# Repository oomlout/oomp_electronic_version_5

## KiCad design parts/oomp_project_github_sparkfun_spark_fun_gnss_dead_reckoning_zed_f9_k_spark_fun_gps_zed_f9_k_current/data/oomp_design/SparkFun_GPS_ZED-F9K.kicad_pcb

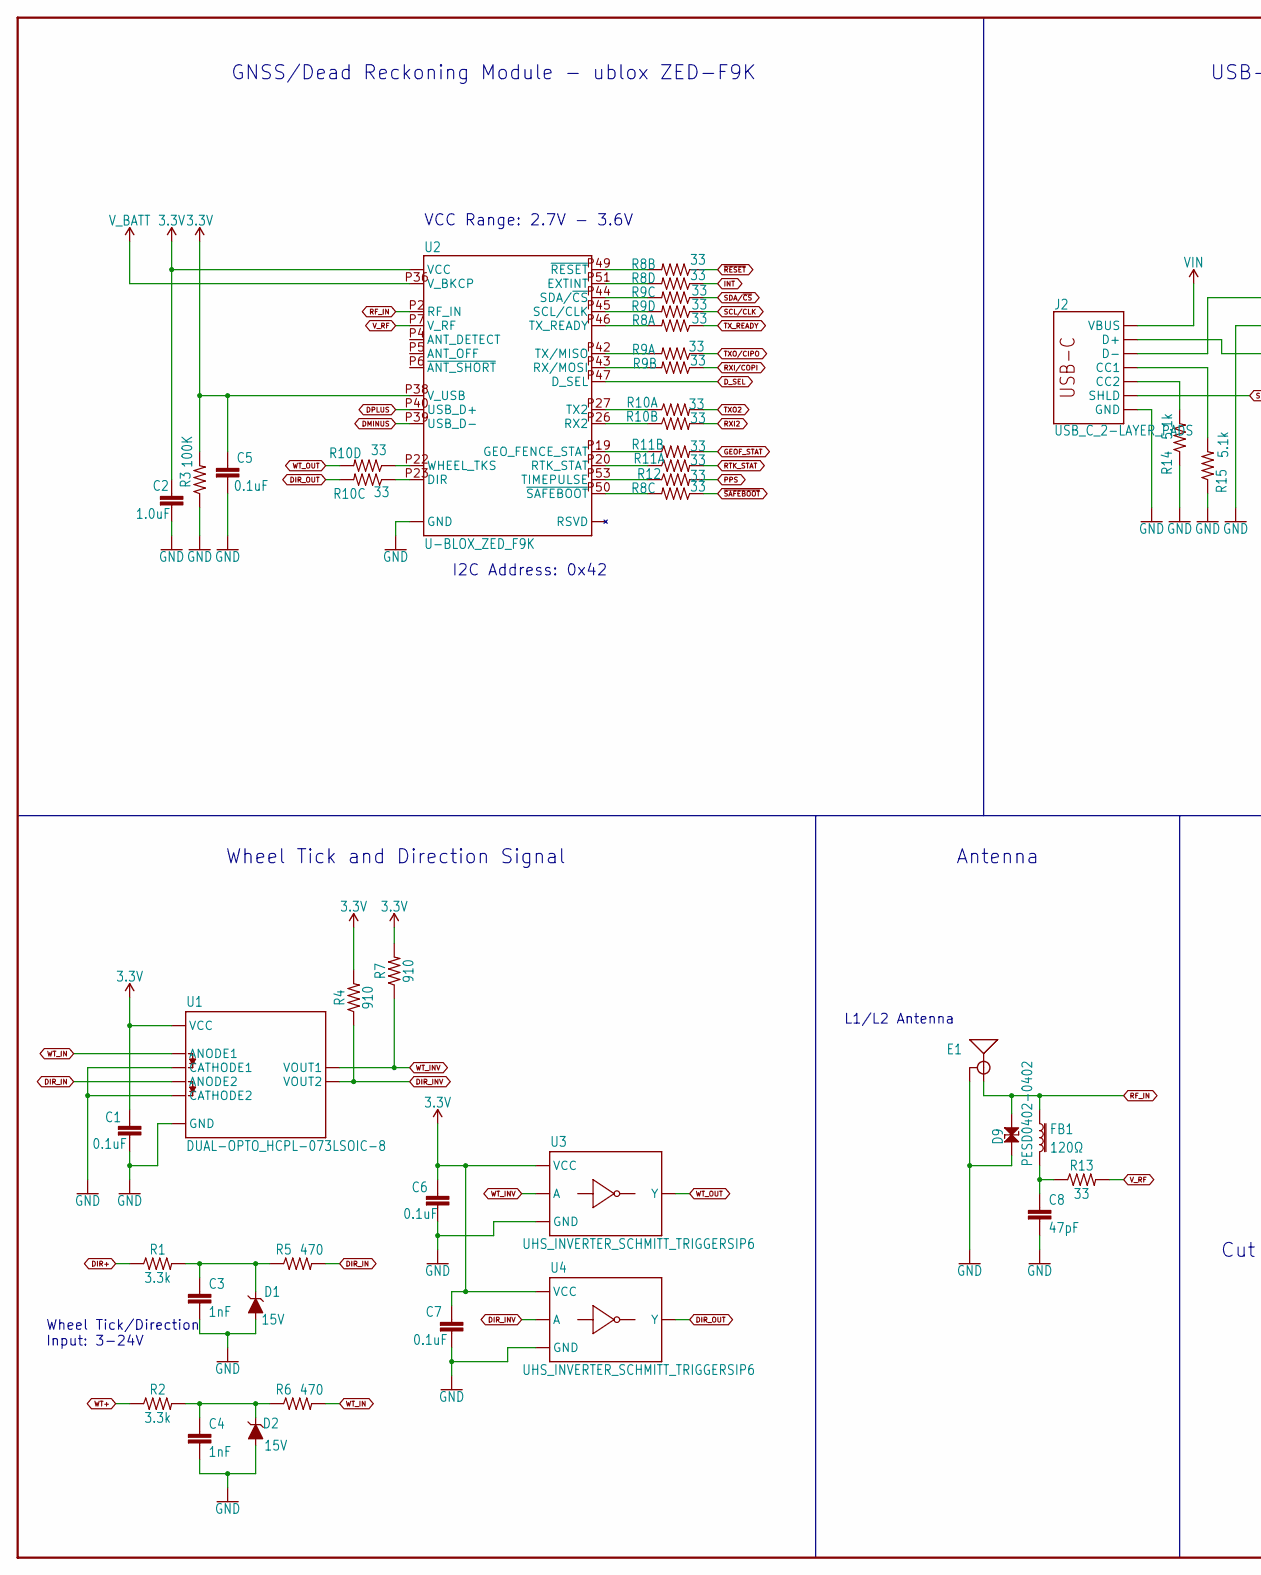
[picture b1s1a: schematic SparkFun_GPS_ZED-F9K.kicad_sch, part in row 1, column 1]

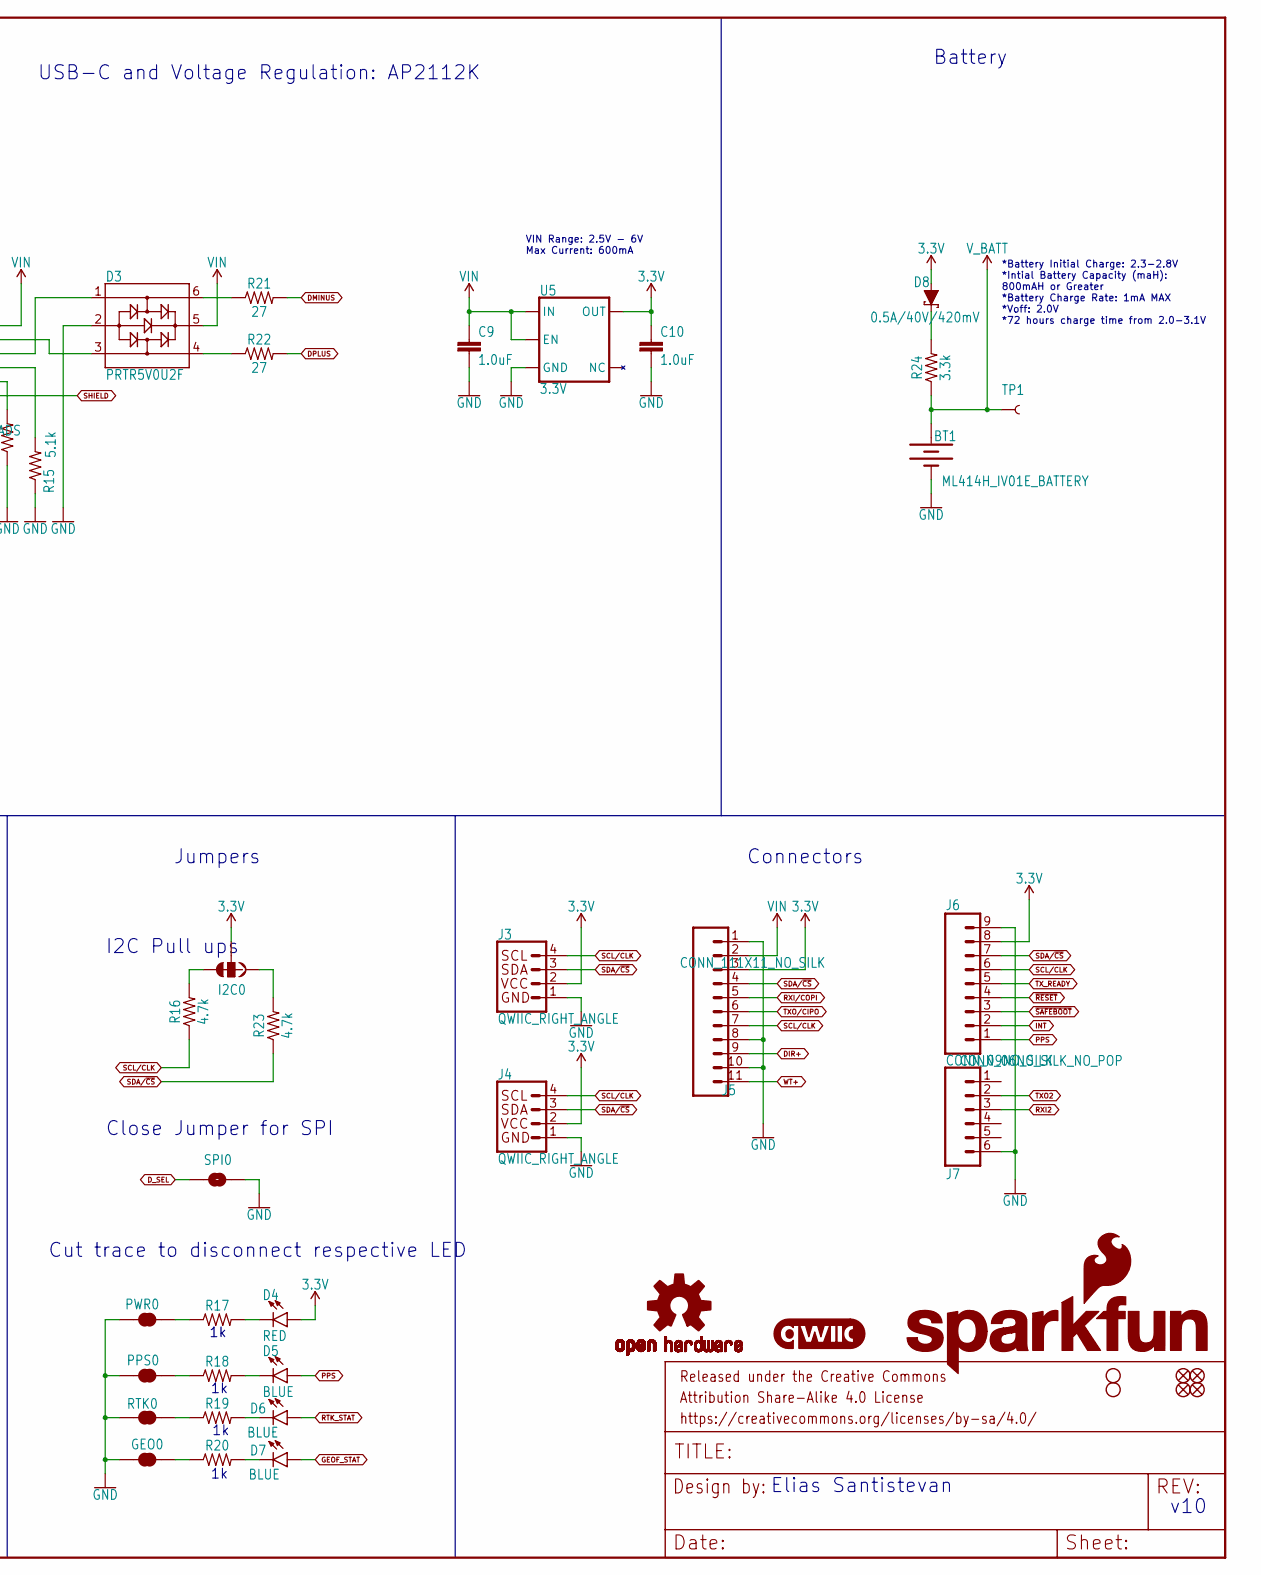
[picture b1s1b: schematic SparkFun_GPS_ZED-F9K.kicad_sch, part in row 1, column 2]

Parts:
$1_25_$_2020-03-30_22-52-05: STAND-OFFTIGHT; STAND-OFF-TIGHT
BT1: ML414H_IV01E_BATTERY; ML414H_IV01E
C1, C5, C6, C7: 0.1uF; 0402-TIGHT
C2, C9, C10: 1.0uF; 0402-TIGHT
C3, C4: 1nF; 0402
C8: 47pF; 0402
D1, D2: 15V; SOT23-3
D3: PRTR5V0U2F; SOT886
D4: RED; LED-0603
D5, D6, D7: BLUE; LED-0603
D8: 0.5A/40V/420mV; SOD-323
D9: PESD0402-0402; 0402; MOUSE_PART 650-PESD0402-140; DIGIKEY_PART PESD0402-140CT-ND
E1: ANTENNA-SMA-GROUNDEDEDGE_SMA; SMA-EDGE
FB1: 120Ω; 0402; MFG_PART BLM15HB121SN1D
FD1, FD2, FD3, FD4: FIDUCIALUFIDUCIAL; FIDUCIAL-MICRO
FRAME1: FRAME-LEDGER; CREATIVE_COMMONS
GEO0: JUMPER-SMT_2_NC_TRACE_SILK; SMT-JUMPER_2_NC_TRACE_SILK
H2: STAND-OFFTIGHT; STAND-OFF-TIGHT
I2C0: JUMPER-SMT_3_2-NC_TRACE_SILK; SMT-JUMPER_3_2-NC_TRACE_SILK
J2: USB_C_2-LAYER_PADS; USB-C-16P-2LAYER-PADS
J3, J4: QWIIC_RIGHT_ANGLE; JST04_1MM_RA
J5: CONN_111X11_NO_SILK; 1X11_NO_SILK
J6: CONN_09NO_SILK; 1X09_NO_SILK
J7: CONN_06NO_SILK_NO_POP; 1X06_NO_SILK
LOGO1: OSHW-LOGOS; OSHW-LOGO-S
LOGO2: QWIIC_LOGO_4MM; QWIIC_4MM
LOGO3: SFE_LOGO_NAME_FLAME.2_INCH; SFE_LOGO_NAME_FLAME_.2
PPS0: JUMPER-SMT_2_NC_TRACE_SILK; SMT-JUMPER_2_NC_TRACE_SILK
PWR0: JUMPER-SMT_2_NC_TRACE_SILK; SMT-JUMPER_2_NC_TRACE_SILK
R1, R2, R24: 3.3k; 0603
R3: 100K; 0402
R4, R7: 910; 0603
R5, R6: 470; 0603
R8, R9, R10, R11: 33; 1206_RA
R12, R13: 33; 0603
R14, R15: 5.1k; 0402
R16, R23: 4.7k; 0402-TIGHT
R17, R18, R19, R20: 1KOHM-0402-1/16W-1%; 0402
R21, R22: 27; 0603
RTK0: JUMPER-SMT_2_NC_TRACE_SILK; SMT-JUMPER_2_NC_TRACE_SILK
SPI0: JUMPER-SMT_2_NO_SILK; SMT-JUMPER_2_NO_SILK
TP1: TEST-POINT3X5; PAD.03X.05
U1: DUAL-OPTO_HCPL-073LSOIC-8; SO08
U2: U-BLOX_ZED_F9K; UBLOX_ZED_F9K
U3, U4: UHS_INVERTER_SCHMITT_TRIGGERSIP6; SIP6
U5: 3.3V; SOT23-5

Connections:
3.3V: C1.1, C2.1, C5.1, C6.1, C7.1, C10.1, D4.A, D8.A, I2C0.2, J3.2, J4.2, J5.3, J6.8, R3.2, R4.2, R7.2, U1.8 (VCC), U2.P33 (VCC), U2.P34 (VCC), U2.P38 (V_USB), U3.P6 (VCC), U4.P6 (VCC), U5.5 (OUT)
DIR+: J5.9, R1.1
DIR_IN: R5.2, U1.4 (ANODE2)
DIR_INV: R4.1, U1.6 (VOUT2), U4.P2 (A)
DIR_OUT: R10.P6 (2), U4.P4 (Y)
DMINUS: R21.2, U2.P39 (USB_D-)
DPLUS: R22.2, U2.P40 (USB_D+)
D_SEL: SPI0.1, U2.P47 (D_SEL)
GEOF_STAT: D7.A, R11.P7 (2)
GND: BT1.-, C1.2, C2.2, C3.2, C4.2, C5.2, C6.2, C7.2, C8.2, C9.2, C10.2, D1.1 (A), D2.1 (A), D3.2, D9.1, E1.GND@0 (GND), E1.GND@1 (GND), E1.GND@2 (GND), E1.GND@3 (GND), GEO0.1, J2.GND, J2.GND2 (GND), J3.1, J4.1, J5.1, J5.8, J5.10, J6.9, J7.6, PPS0.1, PWR0.1, R3.1, R14.1, R15.1, RTK0.1, SPI0.2, U1.2 (CATHODE1), U1.3 (CATHODE2), U1.5 (GND), U2.G1 (GND), U2.G2 (GND), U2.G3 (GND), U2.G4 (GND), U2.G5 (GND), U2.G6 (GND), U2.G7 (GND), U2.G8 (GND), U2.G9 (GND), U2.G10 (GND), U2.G11 (GND), U2.G12 (GND), U2.G13 (GND), U2.G14 (GND), U2.G15 (GND), U2.G16 (GND), U2.G17 (GND), U2.G18 (GND), U2.G19 (GND), U2.G20 (GND), U2.G21 (GND), U2.G22 (GND), U2.G23 (GND), U2.G24 (GND), U2.G25 (GND), U2.G26 (GND), U2.G27 (GND), U2.G28 (GND), U2.G29 (GND), U2.G30 (GND), U2.G31 (GND), U2.G32 (GND), U2.G33 (GND), U2.G34 (GND), U2.G35 (GND), U2.G36 (GND), U2.G37 (GND), U2.G38 (GND), U2.G39 (GND), U2.G40 (GND), U2.G41 (GND), U2.G42 (GND), U2.G43 (GND), U2.G44 (GND), U2.G45 (GND), U2.G46 (GND), U2.G47 (GND), U2.G48 (GND), U2.P1 (GND), U2.P3 (GND), U2.P12 (GND), U2.P14 (GND), U2.P32 (GND), U2.P37 (GND), U2.P41 (GND), U2.P48 (GND), U3.P3 (GND), U4.P3 (GND), U5.2 (GND)
INT: J6.2, R8.P4 (1)
unnamed: I2C0.1, R23.2
unnamed: D8.C, R24.2
unnamed: I2C0.3, R16.2
unnamed: D4.C, R17.2
unnamed: C8.1, FB1.2, R13.1
unnamed: D3.3, J2.A6 (D+), J2.B6 (D+)
unnamed: D3.1, J2.A7 (D-), J2.B7 (D-)
unnamed: PWR0.2, R17.1
unnamed: D3.6, R21.1
unnamed: D3.4, R22.1
unnamed: R8.P7 (2), U2.P49 (~RESET)
unnamed: R8.P5 (2), U2.P51 (EXTINT)
unnamed: J2.B5 (CC2), R14.2
unnamed: J2.A5 (CC1), R15.2
unnamed: R9.P6 (2), U2.P44 (SDA/~CS)
unnamed: R9.P5 (2), U2.P45 (SCL/CLK)
unnamed: R8.P8 (2), U2.P46 (TX_READY)
unnamed: R9.P8 (2), U2.P42 (TX/MISO)
unnamed: R9.P7 (2), U2.P43 (RX/MOSI)
unnamed: R10.P1 (1), U2.P27 (TX2)
unnamed: R19.1, RTK0.2
unnamed: PPS0.2, R18.1
unnamed: D5.C, R18.2
unnamed: D6.C, R19.2
unnamed: R10.P2 (1), U2.P26 (RX2)
unnamed: R11.P2 (1), U2.P19 (GEO_FENCE_STAT)
unnamed: R11.P1 (1), U2.P20 (RTK_STAT)
unnamed: R12.1, U2.P53 (TIMEPULSE)
unnamed: R8.P6 (2), U2.P50 (~SAFEBOOT)
unnamed: R10.P4 (1), U2.P22 (WHEEL_TKS)
unnamed: R10.P3 (1), U2.P23 (DIR)
unnamed: GEO0.2, R20.1
unnamed: D7.C, R20.2
unnamed: C4.1, D2.3 (C), R2.2, R6.1
unnamed: C3.1, D1.3 (C), R1.2, R5.1
PPS: D5.A, J6.1, R12.2
RF_IN: D9.2, E1.SIG (SIGNAL), FB1.1, U2.P2 (RF_IN)
RTK_STAT: D6.A, R11.P8 (2)
RXI2: J7.3, R10.P7 (2)
RXI/COPI: J5.5, R9.P2 (1)
SCL/CLK: J3.4, J4.4, J5.7, J6.6, R9.P4 (1), R16.1
SDA/~CS: J3.3, J4.3, J5.4, J6.7, R9.P3 (1), R23.1
SHIELD: J2.SHLD1 (SHLD), J2.SHLD2 (SHLD), J2.SHLD3 (SHLD), J2.SHLD4 (SHLD)
TXO2: J7.2, R10.P8 (2)
TXO/CIPO: J5.6, R9.P1 (1)
TX_READY: J6.5, R8.P1 (1)
VIN: C9.1, D3.5, J2.VBUS1 (VBUS), J2.VBUS2 (VBUS), J5.2, U5.1 (IN), U5.3 (EN)
V_BATT: BT1.+, R24.1, TP1.1, U2.P36 (V_BKCP)
V_RF: R13.2, U2.P7 (V_RF)
WT+: J5.11, R2.1
WT_IN: R6.2, U1.1 (ANODE1)
WT_INV: R7.1, U1.7 (VOUT1), U3.P2 (A)
WT_OUT: R10.P5 (2), U3.P4 (Y)
~RESET: J6.4, R8.P2 (1)
~SAFEBOOT: J6.3, R8.P3 (1)

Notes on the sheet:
Elias Santistevan
Wheel Tick and Direction Signal
Antenna
*Battery Initial Charge: 2.3-2.8V *Intial Battery Capacity (maH): 800mAH or Greater *Battery Charge Rate: 1mA MAX *Voff: 2.0V *72 hours charge time from 2.0-3.1V
Jumpers
v10
Battery
Close Jumper for SPI
Connectors
I2C Address: 0x42
I2C Pull ups
Cut trace to disconnect respective LED
USB-C and Voltage Regulation: AP2112K
GNSS/Dead Reckoning Module - ublox ZED-F9K
VIN Range: 2.5V - 6V Max Current: 600mA
VCC Range: 2.7V - 3.6V
L1/L2 Antenna
Wheel Tick/Direction Input: 3-24V

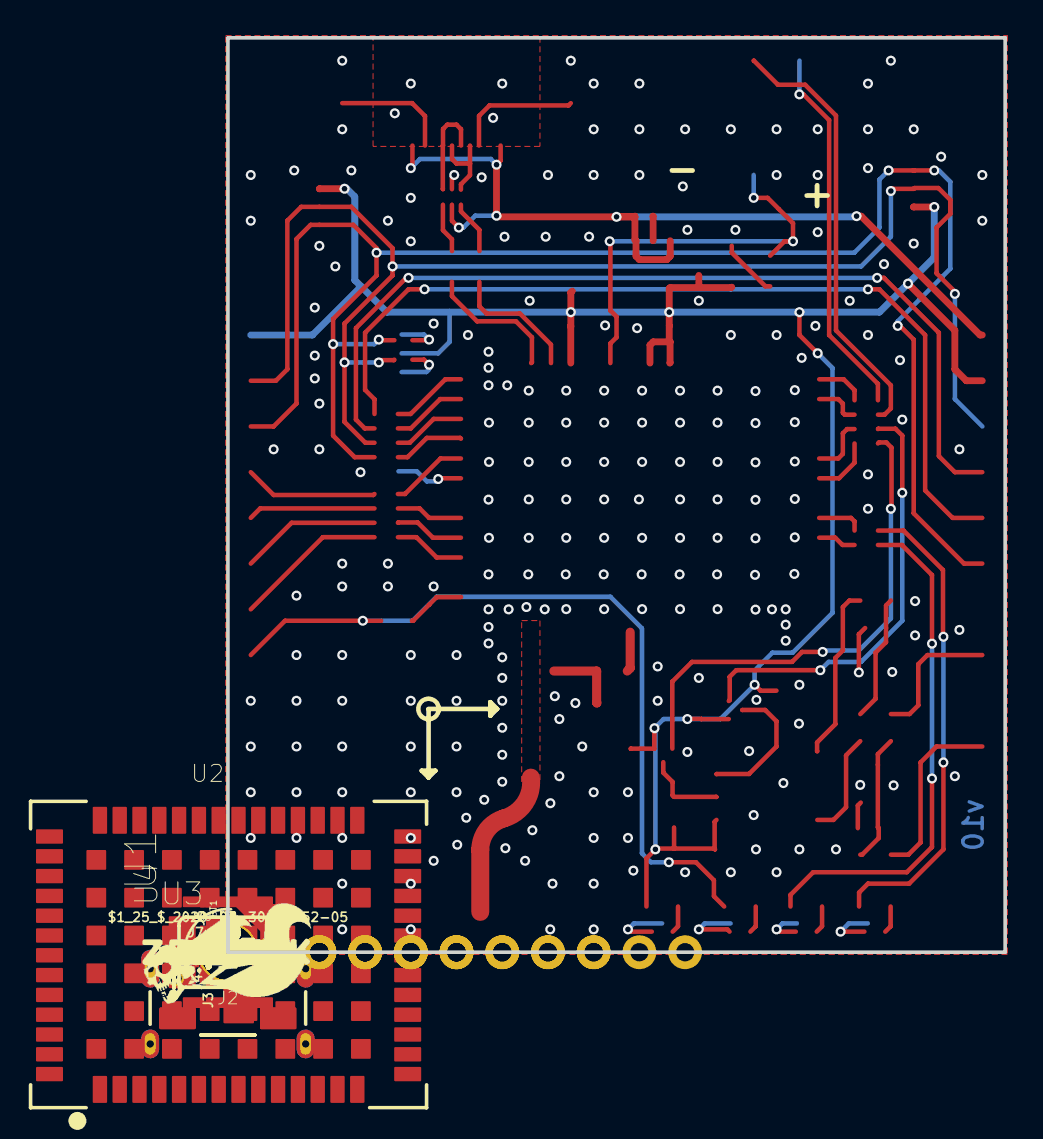
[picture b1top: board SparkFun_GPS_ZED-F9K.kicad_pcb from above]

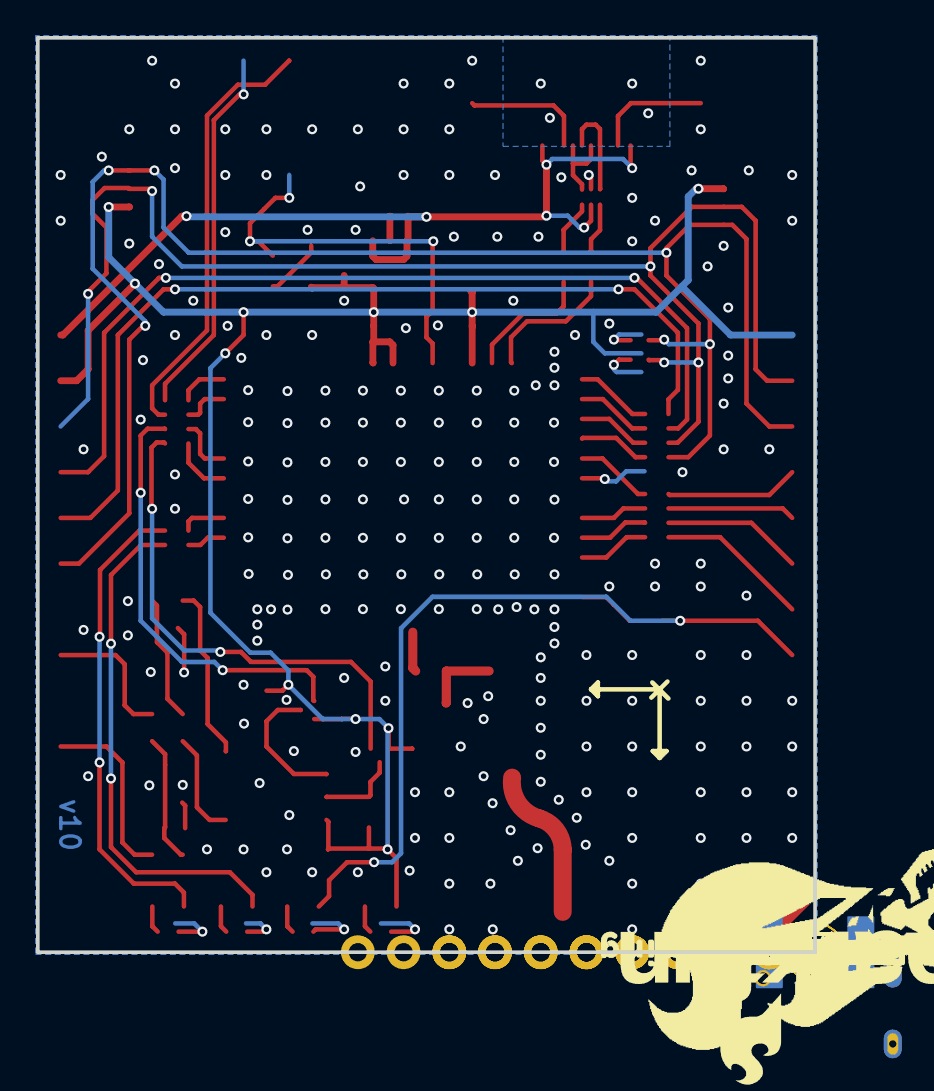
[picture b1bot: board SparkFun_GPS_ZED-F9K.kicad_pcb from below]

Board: 2 copper layers, 43.2 x 50.8 mm, 149 parts (47 on the bottom side), 66 nets.

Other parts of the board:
H1, H4: STAND-OFFTIGHT; STAND-OFF-TIGHT
U$1: PWR22
U$2: PPS21
U$3: GEO23
U$4: RTK24
U$5: #W##16
U$6: #W##15
U$7, U$14, U$22, U$37, U$55: #3V3#6
U$8: #D##13
U$9: #D##14
U$10: #SCK#12
U$11: #CIPO#10
U$12: #COPI#9
U$13: ##CS##11
U$15, U$24: #5V#1
U$16, U$17, U$25, U$36, U$44, U$58: #GND#0
U$18: #TXO2#20
U$19, U$20: DEAD#RECKONING#GPS#BOARD#SILK#FINAL#JPG
U$21: RX224
U$23: BLK225
U$26: GRN226
U$27: #SDA##CS##10
U$28: #RXI#COPI#8
U$30: #SCL#SCK#12
U$31: #D##6
U$32: X1
U$33: #D##7
U$34: #W##4
U$35: #W##5
U$38: #SDA#6
U$39: #SCL#7
U$40: #TXR#3
U$41: ##RST##16
U$42: ##SFBT##17
U$43: #INT#8
U$45: #PPS#0
U$46: #RTK#25
U$47: #GEO#24
U$48: #PPS#21
U$49: L1#L2229
U$50, U$52: Y2
U$51: #PWR#23
U$53: #SPI#22
U$54: #I2C#23
U$56: #SDA#12
U$57, U$63: Z0
U$59: #RXI2#227
U$60: #TXO2#1
U$61: BLK227
U$62: ANTENNA229
U$64: GRN228
U$65: GNSS#DEAD_RECKONING230
U$66: #SCL#13
U$67: #TXR#19
U$68: ##RST##17
U$69: ##SFBT##18
U$70: #INT#14
U$71: #PPS#20
U$72, U$73: ZED#F9K230
U$74: #TXO#CIPO#9

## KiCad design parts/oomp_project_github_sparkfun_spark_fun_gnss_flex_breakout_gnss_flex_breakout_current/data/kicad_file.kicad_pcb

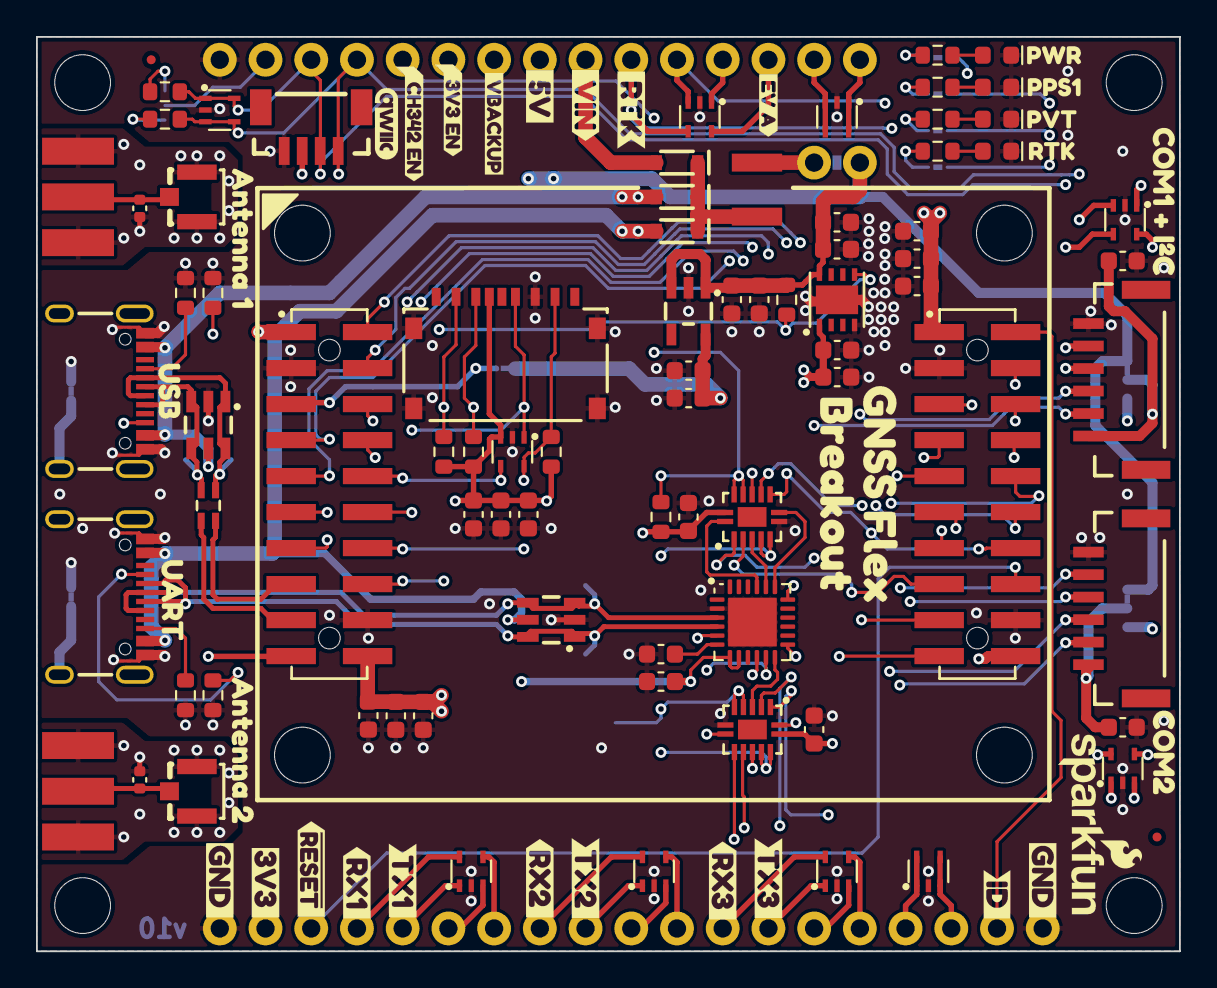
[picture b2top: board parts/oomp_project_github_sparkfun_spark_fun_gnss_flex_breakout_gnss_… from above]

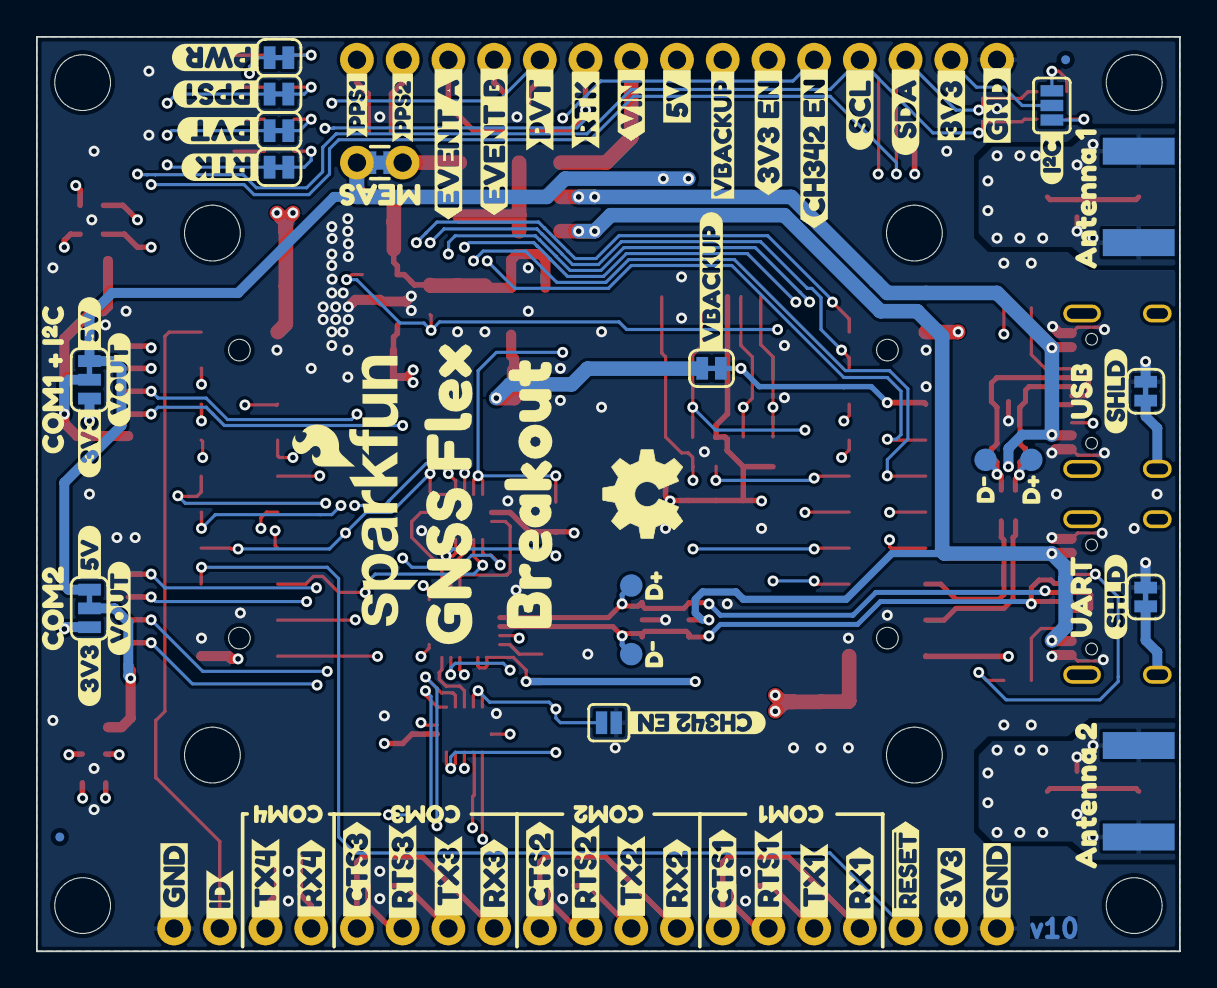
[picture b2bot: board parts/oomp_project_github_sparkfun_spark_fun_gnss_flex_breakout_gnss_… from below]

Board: 4 copper layers, 63.5 x 50.8 mm, 207 parts (85 on the bottom side), 75 nets.

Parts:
C1, C2, C7, C15, C18, C19, C22, C23, C24: 10uF; C_0603_1608Metric
C4, C6, C8, C11: 0.1uF; C_0603_1608Metric
C5, C9, C10, C12, C13, C14, C16, C17, C20, C21: 1.0uF; C_0603_1608Metric
CH342_EN.1: Jumper_2_NO
D1, D7, D8, D10, D11, D12, D13, D14, D15, D16: DF5A5.6LFU; SOT-353
D2: Red; LED_0603_1608Metric_Red
D3: Blue; LED_0603_1608Metric_Blue
D5: White; LED_0603_1608Metric_White
D6: Yellow; LED_0603_1608Metric_Yellow
D9, D20: PESD0402; C_0402_1005Metric
D17, D21: DT1042-04SO; SOT23-6
D18, D19, D22: BAT60A; SOD-323
F1: 6V/2.0A/4.0A; 1210
FID1, FID2, FID3, FID4: Fiducial_0.5mm; Fiducial_0.5mm_Mask1mm
G3: OSHW_Logo; Creative_Commons_License
J1: microSD_Friction; microSD_Friction_Fit_Common
J2, J6: SMA_Edge
J3: Conn_01x15; 1x15
J4: Conn_01x19; 1x19
J5, J13: JST_Locking_6; JST_SMD_1.25mm-6_Locking
J7, J10: USB_C_Receptacle; USB-C_16
J8, J9: U.FL
J11, J12: Conn_02x10; 2x10_2.0mm_Male_Pins_Vertical_SMD_Pegs
J14: Qwiic_Vertical; JST_SMD_1.0mm-4_Vertical_Black
J15: Legend: GNSS Flex; GNSS_Flex_Template
JP1: Measure; Jumper_2_PTH_SMD_Combo-NC
JP2: Jumper_3_NO
PPS1: Jumper_2_NC_Trace
PVT1: Jumper_2_NC_Trace
PWR1: Jumper_2_NC_Trace
R1, R2, R4: 10k; R_0603_1608Metric
R3, R5: 100k; R_0603_1608Metric
R6: 4.7k; R_0603_1608Metric
R7, R8, R9, R12: 2.2k; R_0603_1608Metric
R11: 1k; R_0603_1608Metric
R17, R18, R19, R20: 5.1k; R_0603_1608Metric
RTK1: Jumper_2_NC_Trace
Ref**: Val**; OSHW_Logo_5mm
SHLD1, SHLD2: Jumper_2_NC_Trace
ST1, ST2, ST3, ST4, ST5, ST6, ST7, ST8: Standoff
TP9, TP10, TP12, TP14: 1.25mm; TestPoint-1.25mm
TR2: RFCMF1220100M4T
U1: RT9080-3.3; SOT23-5
U2: CH342F; QFN-24-1EP_4x4mm_P0.5mm_EP2.7x2.7mm
U3, U5: 74HC4066BQ; QFN-14_2.5x3mm_P0.5mm_EP1x1.5mm
U4: AP7361C-3.3V; DFN-8_3x3mm_P0.65mm_EP2.25x1.5mm
VBACKUP.1: Jumper_2_NC_Trace
VOUT1, VOUT2: Jumper_3_NC-1_Trace
kibuzzard-67D04D07: G***; kibuzzard-67D04D07
kibuzzard-67D04D20: G***; kibuzzard-67D04D20
kibuzzard-67D04D30: G***; kibuzzard-67D04D30
kibuzzard-67D04E88: G***; kibuzzard-67D04E88
kibuzzard-67D022A2: G***; kibuzzard-67D022A2
kibuzzard-67D022AC: G***; kibuzzard-67D022AC
kibuzzard-67D044ED, kibuzzard-67D044ED#2: G***; kibuzzard-67D044ED
kibuzzard-67D045AD, kibuzzard-67D045AD#2: G***; kibuzzard-67D045AD
kibuzzard-67D045C9: G***; kibuzzard-67D045C9
kibuzzard-67D045EC: G***; kibuzzard-67D045EC
kibuzzard-67D046A8: G***; kibuzzard-67D046A8
kibuzzard-67D046B5: G***; kibuzzard-67D046B5
kibuzzard-67D046BD: G***; kibuzzard-67D046BD
kibuzzard-67D046CC: G***; kibuzzard-67D046CC
kibuzzard-67D046F7: G***; kibuzzard-67D046F7
kibuzzard-67D046FF: G***; kibuzzard-67D046FF
kibuzzard-67D171AB, kibuzzard-67D171AB#2: G***; kibuzzard-67D171AB
kibuzzard-67D171E5, kibuzzard-67D171E5#2: G***; kibuzzard-67D171E5
kibuzzard-67D1674C: G***; kibuzzard-67D1674C
kibuzzard-67D02274: G***; kibuzzard-67D02274
kibuzzard-67D03584: G***; kibuzzard-67D03584
kibuzzard-67D04501: G***; kibuzzard-67D04501
kibuzzard-67D04612: G***; kibuzzard-67D04612
kibuzzard-67D04639: G***; kibuzzard-67D04639
kibuzzard-67D04669: G***; kibuzzard-67D04669
kibuzzard-67D05112, kibuzzard-67D05112#2: G***; kibuzzard-67D05112
kibuzzard-67D16775: G***; kibuzzard-67D16775
kibuzzard-67DAC0B5, kibuzzard-67DAC0B5#2: G***; kibuzzard-67DAC0B5
kibuzzard-67E6AD3C, kibuzzard-67E6AD3C#2: G***; kibuzzard-67E6AD3C
kibuzzard-67E6AD12, kibuzzard-67E6AD12#2: G***; kibuzzard-67E6AD12
kibuzzard-67E6B1CF, kibuzzard-67E6B1CF#2: G***; kibuzzard-67E6B1CF
kibuzzard-67E6B1E0, kibuzzard-67E6B1E0#2: G***; kibuzzard-67E6B1E0
kibuzzard-67E6B4F7: G***; kibuzzard-67E6B4F7
kibuzzard-67E6B5D1: G***; kibuzzard-67E6B5D1
kibuzzard-67E6B5D6: G***; kibuzzard-67E6B5D6
kibuzzard-67E6B5E0: G***; kibuzzard-67E6B5E0
kibuzzard-67E6B5E7: G***; kibuzzard-67E6B5E7
kibuzzard-67E6B70A: G***; kibuzzard-67E6B70A
kibuzzard-67E6B547: G***; kibuzzard-67E6B547
kibuzzard-67E6B575: G***; kibuzzard-67E6B575
kibuzzard-67E6B720: G***; kibuzzard-67E6B720
kibuzzard-67E6B983: G***; kibuzzard-67E6B983
kibuzzard-67E6BA59: G***; kibuzzard-67E6BA59
kibuzzard-67E6BA73: G***; kibuzzard-67E6BA73
kibuzzard-67E6BA93: G***; kibuzzard-67E6BA93
kibuzzard-67E6BABA: G***; kibuzzard-67E6BABA
kibuzzard-67E6BAD6: G***; kibuzzard-67E6BAD6
kibuzzard-67E6BB49: G***; kibuzzard-67E6BB49
kibuzzard-67E6BB64: G***; kibuzzard-67E6BB64
kibuzzard-67E6BBAF: G***; kibuzzard-67E6BBAF
kibuzzard-67E6BBC6: G***; kibuzzard-67E6BBC6
kibuzzard-67E6C8C9: G***; kibuzzard-67E6C8C9
kibuzzard-67E6C8CF: G***; kibuzzard-67E6C8CF
kibuzzard-67E6C641: G***; kibuzzard-67E6C641
kibuzzard-67E68AA4: G***; kibuzzard-67E68AA4
kibuzzard-67E68AF7: G***; kibuzzard-67E68AF7
kibuzzard-67E68BE1: G***; kibuzzard-67E68BE1
kibuzzard-67E686E5: G***; kibuzzard-67E686E5
kibuzzard-67E688B9: G***; kibuzzard-67E688B9
kibuzzard-67E688C1: G***; kibuzzard-67E688C1
kibuzzard-67E688C9: G***; kibuzzard-67E688C9
kibuzzard-67E688D0: G***; kibuzzard-67E688D0
kibuzzard-67E689B5: G***; kibuzzard-67E689B5
kibuzzard-67E689EA: G***; kibuzzard-67E689EA
kibuzzard-67E68821: G***; kibuzzard-67E68821
kibuzzard-67EE9EE3, kibuzzard-67EE9EE3#2: G***; kibuzzard-67EE9EE3
kibuzzard-67EE9EFF, kibuzzard-67EE9EFF#2: G***; kibuzzard-67EE9EFF
kibuzzard-67EEB40C: G***; kibuzzard-67EEB40C
kibuzzard-67EEB400: G***; kibuzzard-67EEB400
kibuzzard-67EFA2E8: G***; kibuzzard-67EFA2E8
kibuzzard-67EFA2F1: G***; kibuzzard-67EFA2F1
kibuzzard-67EFDE56: G***; kibuzzard-67EFDE56
kibuzzard-67EFEB6F: G***; kibuzzard-67EFEB6F
kibuzzard-67EFEB92: G***; kibuzzard-67EFEB92
kibuzzard-67F7B6D7: G***; kibuzzard-67F7B6D7
kibuzzard-67F7B700: G***; kibuzzard-67F7B700
kibuzzard-67F7C8FB: G***; kibuzzard-67F7C8FB
kibuzzard-67F7C94B: G***; kibuzzard-67F7C94B
kibuzzard-67F7C97D: G***; kibuzzard-67F7C97D
kibuzzard-67F7C969: G***; kibuzzard-67F7C969
kibuzzard-67F7C991: G***; kibuzzard-67F7C991
kibuzzard-682202FA: G***; kibuzzard-682202FA
kibuzzard-6822032F: G***; kibuzzard-6822032F
kibuzzard-68220336: G***; kibuzzard-68220336

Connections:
3.3V: C1.1, C2.1, C4.1, C5.1, C6.1, C7.1, C8.1, C9.1, C10.1, C13.1, C14.1, C17.1, C18.1, D1.3 (K2), J1.4 (VDD), J3.2, J4.2, J11.1, J11.20, J12.1, J12.20, J14.2, JP2.2 (B), PWR1.2 (B), R1.2, R2.2, R4.2, R5.2, U2.5 (VIO), U3.14 (VCC), U4.1 (VOUT), U5.14 (VCC), VOUT1.3 (C), VOUT2.3 (C)
3V3_EN: J3.6, R3.1, U4.5 (EN)
5V: C15.1, C16.1, C19.1, C20.1, J3.8, JP1.2 (B), R3.2, U1.1 (VIN), U1.3 (EN), U4.8 (VIN), VOUT1.1 (A), VOUT2.1 (A)
CH342_EN: CH342_EN.1.2 (B), J3.5, R5.1, U3.5 (2E), U3.6 (3E), U3.12 (4E), U3.13 (1E), U5.5 (2E), U5.6 (3E), U5.12 (4E), U5.13 (1E)
CTS1: D13.4 (K3), J4.7, J12.14, U3.9 (3Z)
CTS2: D12.4 (K3), D14.3 (K2), J4.11, J5.4, J12.7, U5.9 (3Z)
CTS3: D10.4 (K3), J4.15, J12.4
EVENT_A: D8.5 (K4), J3.13, J11.6
EVENT_B: D8.1 (K1), J3.12, J11.8
GND: C1.2, C2.2, C4.2, C5.2, C6.2, C7.2, C8.2, C9.2, C10.2, C11.2, C12.2, C13.2, C14.2, C15.2, C16.2, C17.2, C18.2, C19.2, C20.2, C21.2, C22.2, C23.1, C24.1, CH342_EN.1.1 (A), D1.2 (A), D2.1 (K), D3.1 (K), D5.1 (K), D6.1 (K), D7.2 (A), D8.2 (A), D9.1 (A1), D10.2 (A), D11.2 (A), D12.2 (A), D13.2 (A), D14.2 (A), D15.2 (A), D16.2 (A), D17.2 (GND), D20.1 (A1), D21.2 (GND), J1.6 (VSS), J1.10 (SHIELD), J2.2 (Ext), J3.1, J4.1, J4.19, J5.6, J6.2 (Ext), J7.GND, J8.2 (Ext), J9.2 (Ext), J10.GND, J11.3, J11.18, J12.3, J12.18, J13.6, J14.1, R17.1, R18.1, R19.1, R20.1, SHLD1.1 (A), SHLD2.1 (A), U1.2 (GND), U2.2 (GND), U2.25 (GND), U3.7 (GND), U4.4 (GND), U4.9 (EP), U5.7 (GND)
ID: J4.18, J12.2
unnamed: D2.2 (A), R6.1
unnamed: D3.2 (A), R7.1
unnamed: D5.2 (A), R11.1
unnamed: D6.2 (A), R12.1
unnamed: D9.2 (A2), J2.1 (In), J9.1 (In)
unnamed: D18.1 (K), D19.1 (K), D22.1 (K), F1.1
unnamed: D20.2 (A2), J6.1 (In), J8.1 (In)
unnamed: D21.1 (I/O1), D21.6 (I/O4), J10.A7 (D-), J10.B7 (D-), TP14.1, TR2.1
unnamed: D21.3 (I/O2), D21.4 (I/O3), J10.A6 (D+), J10.B6 (D+), TP10.1, TR2.3
unnamed: C23.2, J5.1, VOUT2.2 (B)
unnamed: J7.A5 (CC1), R18.2
unnamed: J7.B5 (CC2), R17.2
unnamed: J7.S (SHIELD), SHLD2.2 (B)
unnamed: J10.A5 (CC1), R20.2
unnamed: J10.B5 (CC2), R19.2
unnamed: J10.S (SHIELD), SHLD1.2 (B)
unnamed: C24.2, J13.1, VOUT1.2 (B)
unnamed: F1.2, JP1.1 (A)
unnamed: JP2.1 (A), R8.1
unnamed: JP2.3 (C), R9.2
unnamed: PPS1.1 (A), R12.2
unnamed: PVT1.1 (A), R7.2
unnamed: PWR1.1 (A), R6.2
unnamed: R11.2, RTK1.1 (A)
unnamed: C21.1, C22.1, U1.5 (VOUT), VBACKUP.1.1 (A)
unnamed: U2.20 (RXD0), U3.4 (2Y)
unnamed: U2.12 (RXD1), U5.4 (2Y)
unnamed: U2.21 (TXD0), U3.1 (1Y)
unnamed: U2.13 (TXD1), U5.1 (1Y)
unnamed: C11.1, U2.6 (V3)
unnamed: U2.18 (~CTS0), U3.11 (4Y)
unnamed: U2.10 (~CTS1), U5.11 (4Y)
unnamed: U2.19 (~RTS0), U3.8 (3Y)
unnamed: U2.11 (~RTS1), U5.8 (3Y)
PPS1: D7.1 (K1), D7.5 (K4), J3.15, J11.2, PPS1.2 (B)
PPS2: D7.3 (K2), D7.4 (K3), J3.14, J11.4
PVT_LED: D8.3 (K2), J3.11, J11.9, PVT1.2 (B)
RTK_LED: D8.4 (K3), J3.10, J11.7, RTK1.2 (B)
RTS1: D13.3 (K2), J4.6, J12.17, U3.10 (4Z)
RTS2: D12.3 (K2), D14.4 (K3), J4.10, J5.5, J12.9, U5.10 (4Z)
RTS3: D10.3 (K2), J4.14, J12.5
RX1: D13.5 (K4), D16.5 (K4), J4.4, J12.19, J13.2, U3.2 (1Z)
RX2: D12.5 (K4), D14.1 (K1), J4.8, J5.3, J12.12, U5.2 (1Z)
RX3: D10.5 (K4), J4.12, J12.8
RX4: D11.1 (K1), D11.5 (K4), J4.16, J12.13
SCL: D15.3 (K2), D15.4 (K3), D16.3 (K2), J3.4, J11.13, J13.4, J14.4, R9.1
SDA: D15.1 (K1), D15.5 (K4), D16.4 (K3), J3.3, J11.11, J13.5, J14.3, R8.2
SD_CLK: D1.1 (K1), J1.5 (CLK/SCK), J11.12
SD_CMD: D1.4 (K3), J1.3 (CMD/SDI), J11.10, R2.1
SD_DAT0: D1.5 (K4), J1.7 (DAT0/SDO), J11.14, R1.1
SD_DAT3: J1.2 (DAT3/~CS), J11.16, R4.1
TX1: D13.1 (K1), D16.1 (K1), J4.5, J12.15, J13.3, U3.3 (2Z)
TX2: D12.1 (K1), D14.5 (K4), J4.9, J5.2, J12.10, U5.3 (2Z)
TX3: D10.1 (K1), J4.13, J12.6
TX4: D11.3 (K2), D11.4 (K3), J4.17, J12.11
USB1_D+: J11.17, TR2.4
USB1_D-: J11.15, TR2.2
USB2_D+: D17.3 (I/O2), D17.4 (I/O3), J7.A6 (D+), J7.B6 (D+), TP9.1, U2.3 (UD+)
USB2_D-: D17.1 (I/O1), D17.6 (I/O4), J7.A7 (D-), J7.B7 (D-), TP12.1, U2.4 (UD-)
VBACKUP: J3.7, J11.5, VBACKUP.1.2 (B)
VIN: D19.2 (A), J3.9
VUSB1: D18.2 (A), D21.5 (VCC), J10.VBUS, J11.19
VUSB2: C12.1, D17.5 (VCC), D22.2 (A), J7.VBUS, U2.7 (VDD5), U2.8 (VBUS)
~RESET: J4.3, J12.16

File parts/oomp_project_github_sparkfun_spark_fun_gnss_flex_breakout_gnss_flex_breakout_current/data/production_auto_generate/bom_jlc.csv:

Comment,Designator,Footprint,LCSC Part #
0.1uF,"C4,C6,C8,C11",SparkFun-Capacitor:C_0603_1608Metric,C14663
1.0uF,"C5,C9,C10,C12,C13,C14,C16,C17,C20,C21",SparkFun-Capacitor:C_0603_1608Metric,C5673
1.25mm,"TP9,TP10,TP12,TP14",SparkFun-Connector:TestPoint-1.25mm,
100k,"R3,R5",SparkFun-Resistor:R_0603_1608Metric,C25803
10k,"R1,R2,R4",SparkFun-Resistor:R_0603_1608Metric,C98220
10uF,"C1,C2,C7,C15,C18,C19,C22,C23,C24",SparkFun-Capacitor:C_0603_1608Metric,C19702
1k,R11,SparkFun-Resistor:R_0603_1608Metric,C2907002
2.2k,"R7,R8,R9,R12",SparkFun-Resistor:R_0603_1608Metric,C4190
4.7k,R6,SparkFun-Resistor:R_0603_1608Metric,C23162
5.1k,"R17,R18,R19,R20",SparkFun-Resistor:R_0603_1608Metric,C23186
6V/2.0A/4.0A,F1,SparkFun-Fuse:1210,
74HC4066BQ,"U3,U5",SparkFun-Semiconductor-Standard:QFN-14_2.5x3mm_P0.5mm_EP1x1.5mm,
AP7361C-3.3V,U4,SparkFun-Semiconductor-Standard:DFN-8_3x3mm_P0.65mm_EP2.25x1.5mm,
BAT60A,"D18,D19,D22",SparkFun-Semiconductor-Standard:SOD-323,
Blue,D3,SparkFun-LED:LED_0603_1608Metric_Blue,
CH342F,U2,SparkFun-Semiconductor-Standard:QFN-24-1EP_4x4mm_P0.5mm_EP2.7x2.7mm,
Conn_01x15,J3,SparkFun-Connector:1x15,C7501589
Conn_01x19,J4,SparkFun-Connector:1x19,C2894942
Conn_02x10,"J11,J12",SparkFun-Connector:2x10_2.0mm_Male_Pins_Vertical_SMD_Pegs,
DF5A5.6LFU,"D1,D7,D8,D10,D11,D12,D13,D14,D15,D16",SparkFun-Semiconductor-Standard:SOT-353,C5445
DT1042-04SO,"D17,D21",SparkFun-Semiconductor-Standard:SOT23-6,C460064
JST_Locking_6,"J5,J13",SparkFun-Connector:JST_SMD_1.25mm-6_Locking,
Measure,JP1,SparkFun-Jumper:Jumper_2_PTH_SMD_Combo-NC,
microSD_Friction,J1,SparkFun-Connector:microSD_Friction_Fit_Common,
PESD0402,"D9,D20",SparkFun-Capacitor:C_0402_1005Metric,C316059
Qwiic_Vertical,J14,SparkFun-Connector:JST_SMD_1.0mm-4_Vertical_Black,C160390
Red,D2,SparkFun-LED:LED_0603_1608Metric_Red,
RFCMF1220100M4T,TR2,SparkFun-Coil:RFCMF1220100M4T,
RT9080-3.3,U1,SparkFun-Semiconductor-Standard:SOT23-5,
SMA_Edge,"J2,J6",SparkFun-Connector:SMA_Edge,
U.FL,"J8,J9",SparkFun-Connector:U.FL,
USB_C_Receptacle,"J7,J10",SparkFun-Connector:USB-C_16,C2765186
White,D5,SparkFun-LED:LED_0603_1608Metric_White,
Yellow,D6,SparkFun-LED:LED_0603_1608Metric_Yellow,
~,"PPS1,PVT1,PWR1,RTK1,SHLD1,SHLD2,VBACKUP.1",SparkFun-Jumper:Jumper_2_NC_Trace,
~,CH342_EN.1,SparkFun-Jumper:Jumper_2_NO,
~,"VOUT1,VOUT2",SparkFun-Jumper:Jumper_3_NC-1_Trace,
~,JP2,SparkFun-Jumper:Jumper_3_NO,

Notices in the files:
parts/oomp_project_github_sparkfun_spark_fun_gnss_function_board_neo_m9_n_spark_fun_gnss_neo_m9_n_current/data/kicad_file.kicad_sch:
Released under the Creative Commons
https://creativecommons.org/licenses/by-sa/4.0
parts and their libraries:
Released under the Creative Commons Attribution Share-Alike 4.0 License
